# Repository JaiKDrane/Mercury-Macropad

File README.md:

# Mercury

## License

This repository uses a split licensing model:

* **Hardware & CAD ('/hardware', '/cad'):** Licensed under the **CERN Open Hardware Licence Version 2 - Strongly Reciprocal** ([CERN-OHL-S v2](LICENSE-HARDWARE.txt))
* **Firmware ('/firmware'):** Licensed under the **GNU General Public License v3.0** ([GPLv3](firmware/LICENSE)) due to QMK dependencies.

## Purpose
The Mercury macropad is a 9+1 key macro pad aimed at being useful for a variety of purposes, the specifications of which is entirely up to the one who makes it. The design is centered around a nice!nano and nice!view, as well as Hotswap Kalih MX switches with Cherry MX stabilizer footprints. Further information can be found in [Bill of Materials](BillOfMaterials.txt).

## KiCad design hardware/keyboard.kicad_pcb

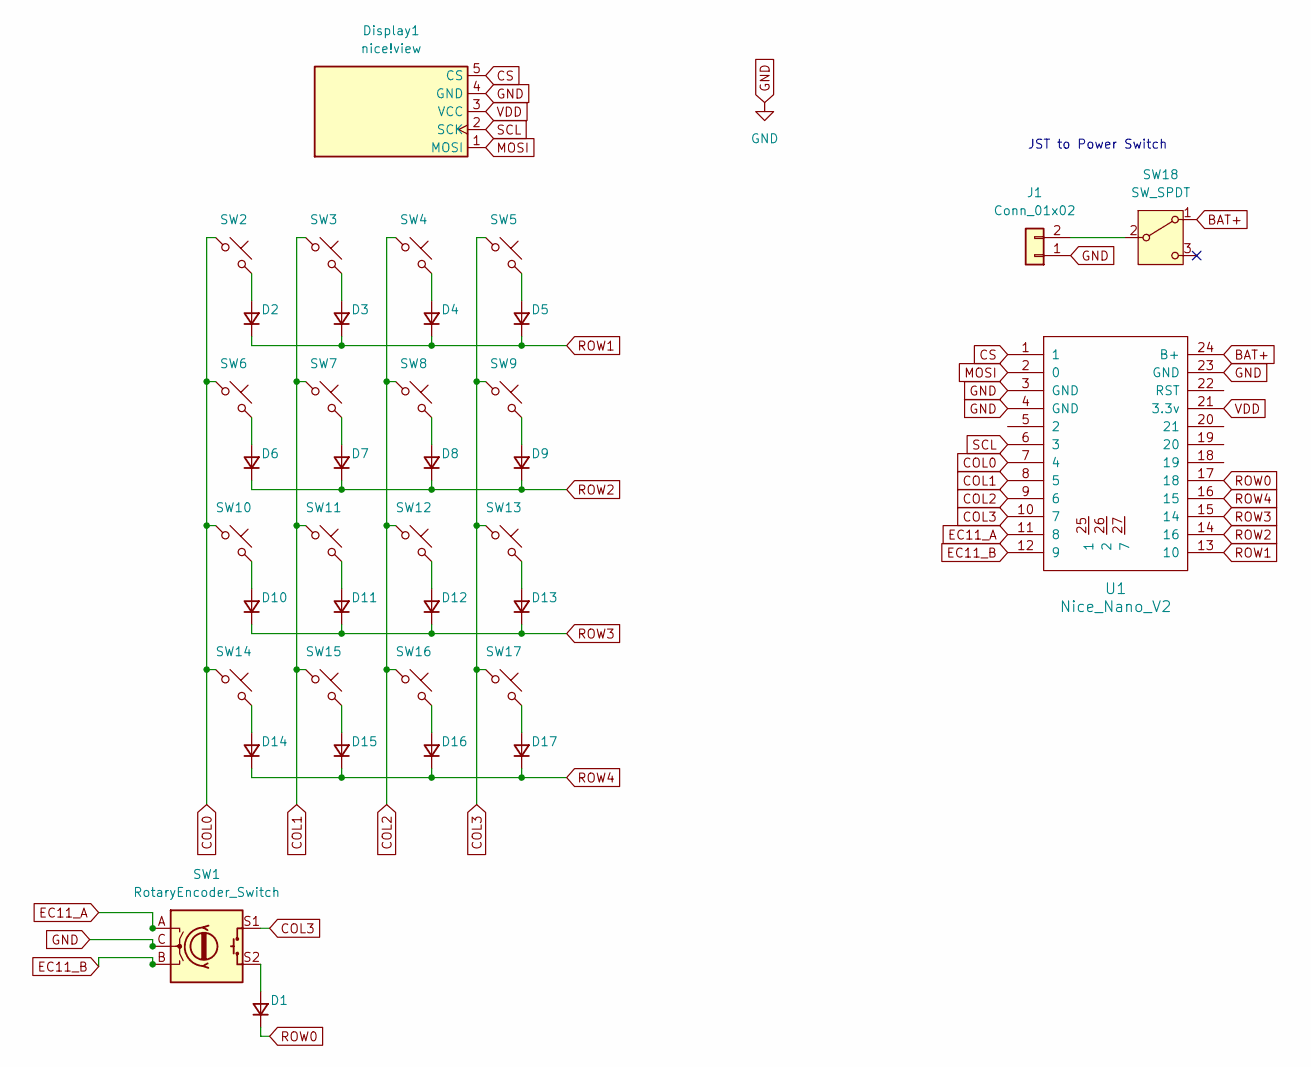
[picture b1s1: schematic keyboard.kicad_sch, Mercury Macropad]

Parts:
D1, D2, D3, D4, D5, D6, D7, D8, D9, D10, D11, D12, D13, D14, D15, D16, D17: D; D_SOD-123
Display1: nice!view; nice_view
J1: Conn_01x02; Tag-Connect_TC2030-IDC-FP_2x03_P1.27mm_Vertical
SW1: RotaryEncoder_Switch; RotaryEncoder_Alps_EC11E-Switch_Vertical_H20mm
SW2, SW3, SW4, SW5, SW6, SW7, SW8, SW9, SW10, SW11, SW12, SW13, SW14, SW15, SW16, SW17: SW_Push; SW_Hotswap_Kailh_MX_1.00u
SW18: SW_SPDT; Nidec_Copal_CAS-120A
U1: Nice_Nano_V2

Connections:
BAT+: SW18.1 (A), U1.24 (B+)
COL0: SW2.1, SW6.1, SW10.1, SW14.1, U1.7 (4)
COL1: SW3.1, SW7.1, SW11.1, SW15.1, U1.8 (5)
COL2: SW4.1, SW8.1, SW12.1, SW16.1, U1.9 (6)
COL3: SW1.S1, SW5.1, SW9.1, SW13.1, SW17.1, U1.10 (7)
CS: Display1.5 (CS), U1.1
EC11_A: SW1.A, U1.11 (8)
EC11_B: SW1.B, U1.12 (9)
GND: Display1.4 (GND), J1.1, SW1.C, U1.3 (GND), U1.4 (GND), U1.23 (GND)
MOSI: Display1.1 (MOSI), U1.2 (0)
unnamed: D1.2 (A), SW1.S2
unnamed: D2.2 (A), SW2.2
unnamed: D3.2 (A), SW3.2
unnamed: D4.2 (A), SW4.2
unnamed: D5.2 (A), SW5.2
unnamed: D6.2 (A), SW6.2
unnamed: D7.2 (A), SW7.2
unnamed: D8.2 (A), SW8.2
unnamed: D9.2 (A), SW9.2
unnamed: D10.2 (A), SW10.2
unnamed: D11.2 (A), SW11.2
unnamed: D12.2 (A), SW12.2
unnamed: D13.2 (A), SW13.2
unnamed: D14.2 (A), SW14.2
unnamed: D15.2 (A), SW15.2
unnamed: D16.2 (A), SW16.2
unnamed: D17.2 (A), SW17.2
unnamed: J1.2, SW18.2 (B)
ROW0: D1.1 (K), U1.17 (18)
ROW1: D2.1 (K), D3.1 (K), D4.1 (K), D5.1 (K), U1.13 (10)
ROW2: D6.1 (K), D7.1 (K), D8.1 (K), D9.1 (K), U1.14 (16)
ROW3: D10.1 (K), D11.1 (K), D12.1 (K), D13.1 (K), U1.15 (14)
ROW4: D14.1 (K), D15.1 (K), D16.1 (K), D17.1 (K), U1.16 (15)
SCL: Display1.2 (SCK), U1.6 (3)
VDD: Display1.3 (VCC), U1.21 (3.3v)

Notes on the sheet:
JST to Power Switch

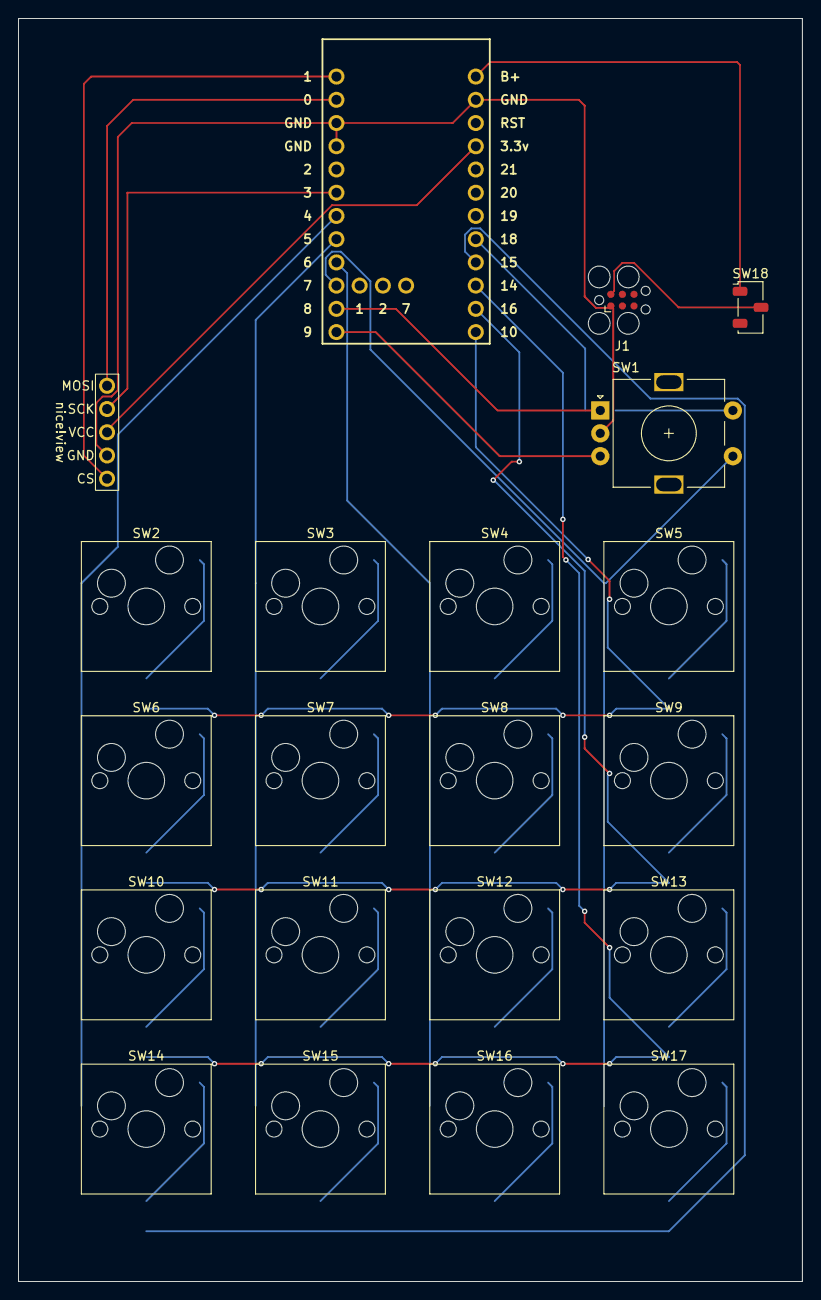
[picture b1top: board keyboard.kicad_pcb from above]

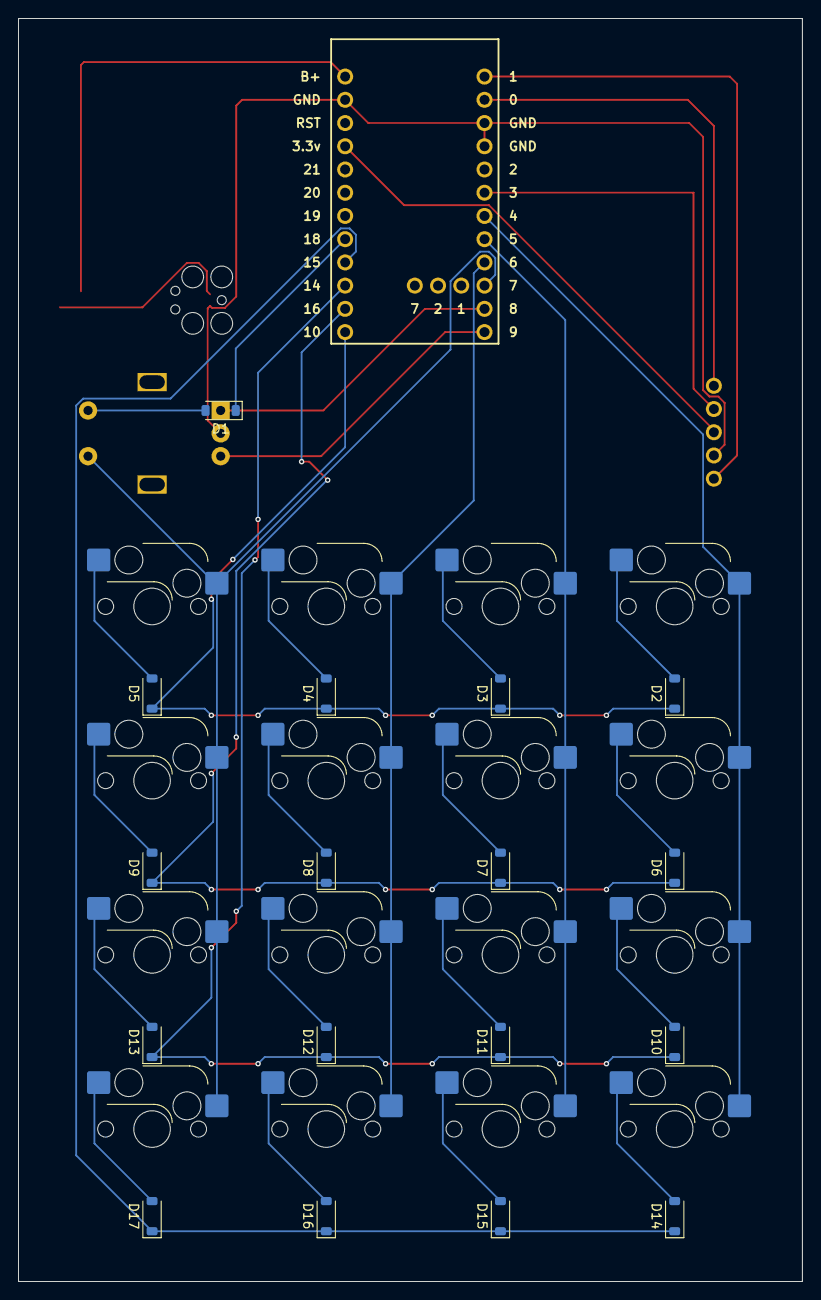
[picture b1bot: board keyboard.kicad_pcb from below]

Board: 2 copper layers, 85.7 x 138.1 mm, 38 parts (17 on the bottom side), 35 nets.
